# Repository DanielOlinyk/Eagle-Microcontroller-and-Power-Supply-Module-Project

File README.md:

# Eagle Microcontroller and Power Supply Module Project
PCB design project of a regulated voltage power module controlling the data processing operations of a 328 microcontroller.

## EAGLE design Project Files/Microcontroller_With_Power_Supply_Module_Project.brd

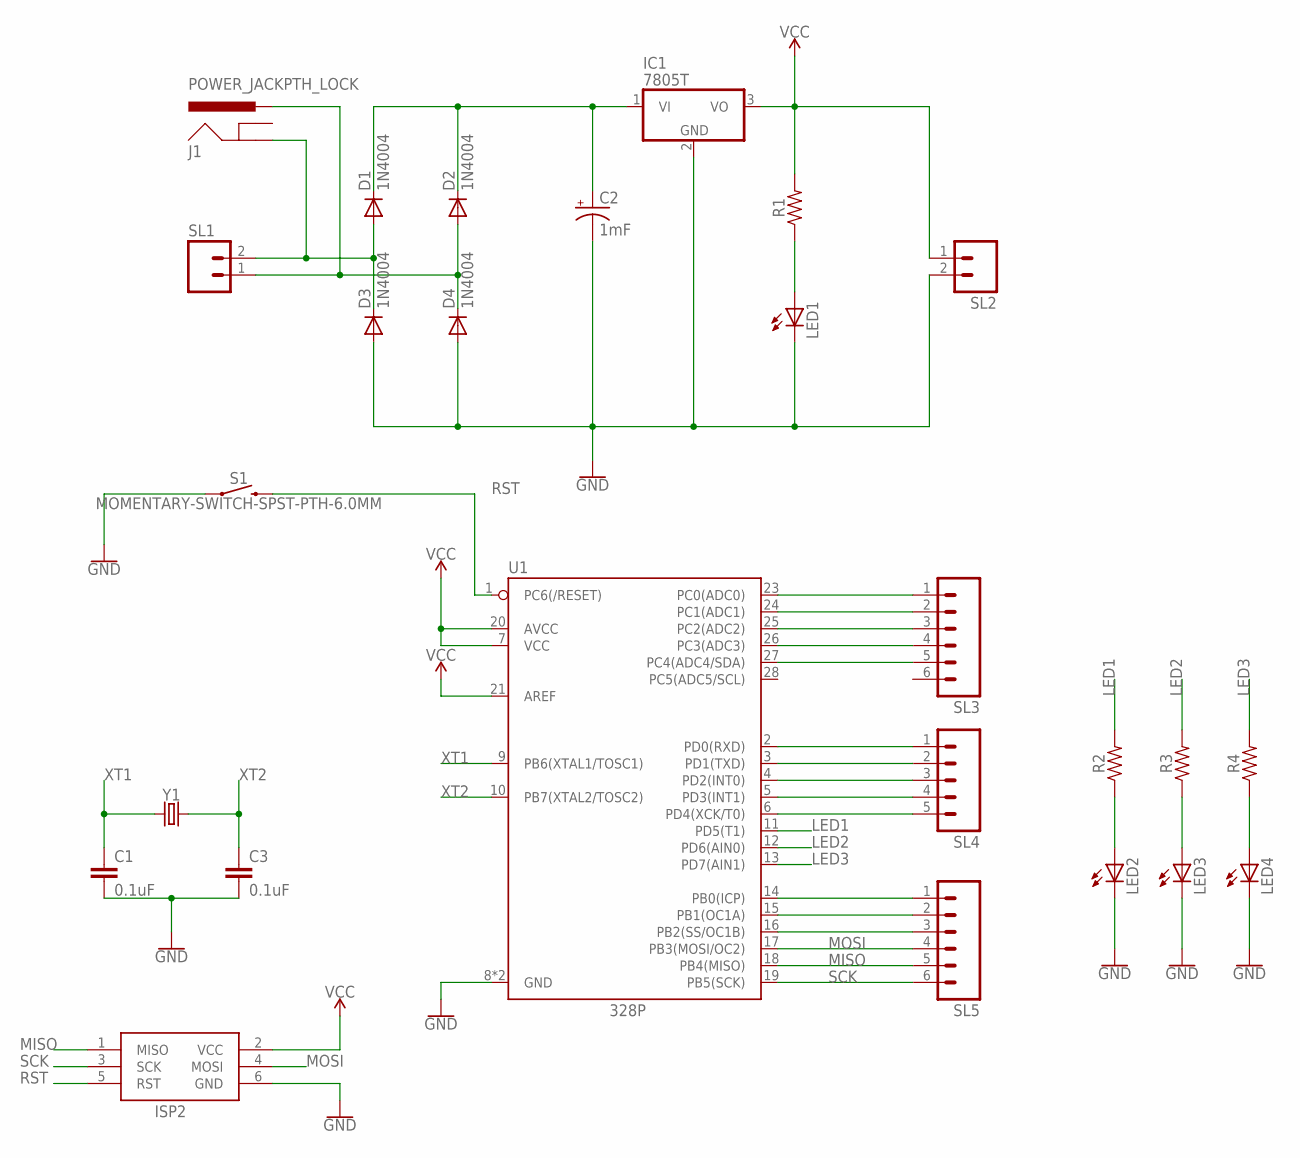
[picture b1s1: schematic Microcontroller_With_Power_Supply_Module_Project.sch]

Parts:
C1, C3: 0.1uF; CAP-PTH-SMALL-KIT
C2: 1mF; CPOL-RADIAL-5MM-10MM
D1, D2, D3, D4: 1N4004; DO41-10
IC1: 7805T; TO220H
ISP2: AVRISP-6; AVRISP
J1: POWER_JACKPTH_LOCK; POWER_JACK_PTH_LOCK
LED1: LED5MM
LED2, LED3, LED4: LED3MM
R1, R2, R3, R4: AXIAL-0.3
S1: MOMENTARY-SWITCH-SPST-PTH-6.0MM; TACTILE_SWITCH_PTH_6.0MM
SL1, SL2: M02; 02P
SL3, SL5: M06; 06P
SL4: M05; 05P
U1: 328P; DIP28
Y1: CRYSTALPTH-HC49US; HC49US

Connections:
GND: C1.2, C2.-, C3.2, D3.A, D4.A, IC1.2 (GND), ISP2.6 (GND), LED1.K (C), LED2.K (C), LED3.K (C), LED4.K (C), S1.1, SL2.2, U1.8 (GND), U1.22 (GND)
LED1: R2.P$2 (2), U1.11 (PD5(T1))
LED2: R3.P$2 (2), U1.12 (PD6(AIN0))
LED3: R4.P$2 (2), U1.13 (PD7(AIN1))
MISO: ISP2.1 (MISO), SL5.5, U1.18 (PB4(MISO))
MOSI: ISP2.4 (MOSI), SL5.4, U1.17 (PB3(MOSI/OC2))
unnamed: D1.A, D3.C, J1.GND, SL1.2
unnamed: D2.A, D4.C, J1.PWR, SL1.1
unnamed: C2.+, D1.C, D2.C, IC1.1 (VI)
unnamed: LED4.A, R4.P$1 (1)
unnamed: LED1.A, R1.P$1 (1)
unnamed: LED3.A, R3.P$1 (1)
unnamed: LED2.A, R2.P$1 (1)
unnamed: SL3.1, U1.23 (PC0(ADC0))
unnamed: SL3.2, U1.24 (PC1(ADC1))
unnamed: SL3.3, U1.25 (PC2(ADC2))
unnamed: SL3.4, U1.26 (PC3(ADC3))
unnamed: SL3.5, U1.27 (PC4(ADC4/SDA))
unnamed: SL4.1, U1.2 (PD0(RXD))
unnamed: SL4.2, U1.3 (PD1(TXD))
unnamed: SL4.3, U1.4 (PD2(INT0))
unnamed: SL4.4, U1.5 (PD3(INT1))
unnamed: SL4.5, U1.6 (PD4(XCK/T0))
unnamed: SL5.1, U1.14 (PB0(ICP))
unnamed: SL5.2, U1.15 (PB1(OC1A))
unnamed: SL5.3, U1.16 (PB2(SS/OC1B))
RST: ISP2.5 (RST), S1.3 (2), U1.1 (PC6(/RESET))
SCK: ISP2.3 (SCK), SL5.6, U1.19 (PB5(SCK))
VCC: IC1.3 (VO), ISP2.2 (VCC), R1.P$2 (2), SL2.1, U1.7 (VCC), U1.20 (AVCC), U1.21 (AREF)
XT1: C1.1, U1.9 (PB6(XTAL1/TOSC1)), Y1.1
XT2: C3.1, U1.10 (PB7(XTAL2/TOSC2)), Y1.2

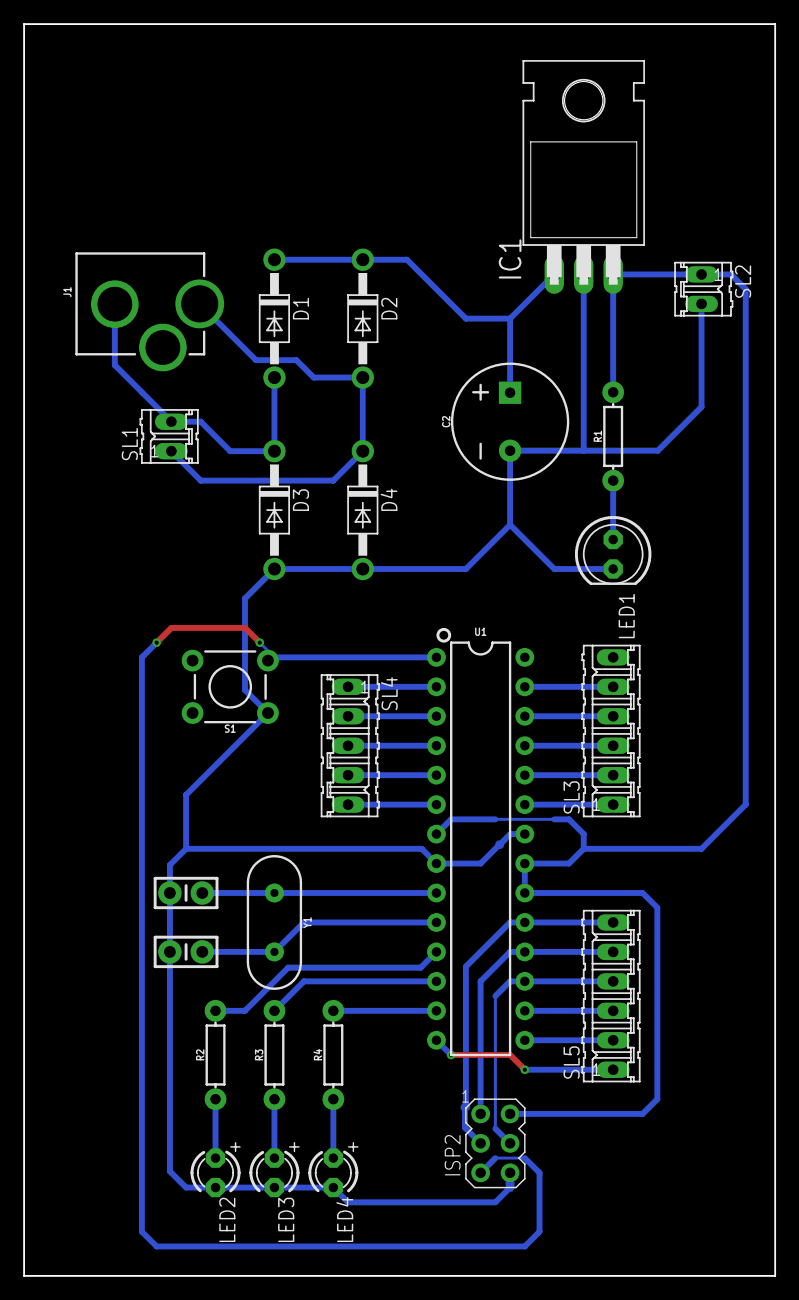
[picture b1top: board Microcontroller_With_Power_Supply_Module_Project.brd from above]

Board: 2 copper layers, 64.8 x 108.0 mm, 26 parts (0 on the bottom side), 31 nets.

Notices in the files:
parts and their libraries:
SparkFun-Capacitors: Licensing: Creative Commons ShareAlike 4.0 International - https://creativecommons.org/licenses/by-sa/4.0
